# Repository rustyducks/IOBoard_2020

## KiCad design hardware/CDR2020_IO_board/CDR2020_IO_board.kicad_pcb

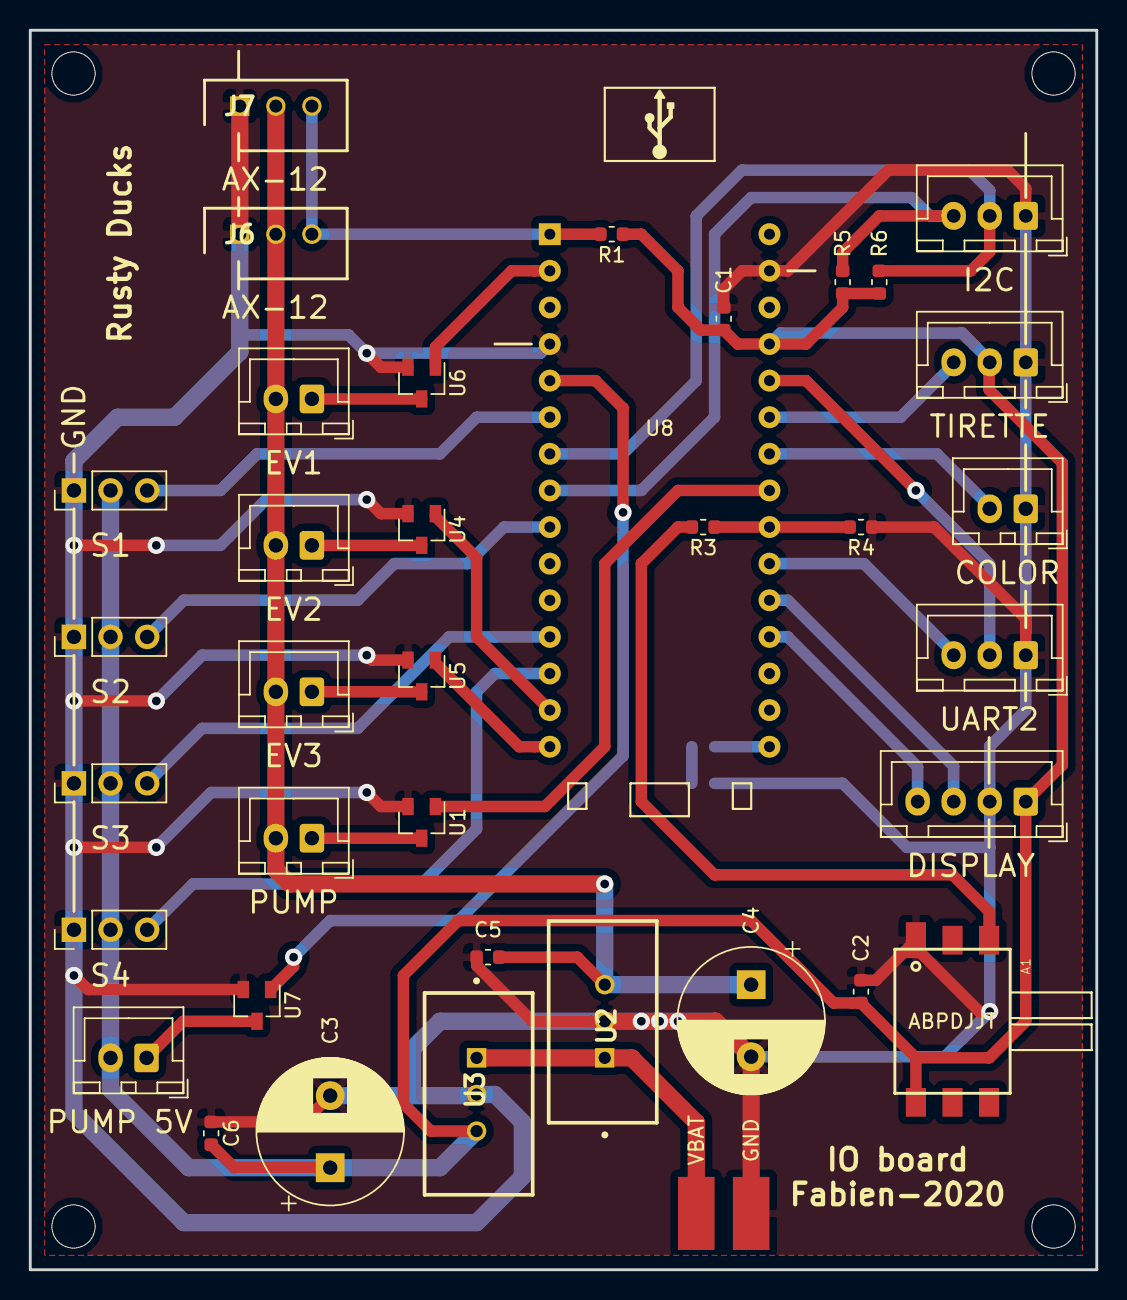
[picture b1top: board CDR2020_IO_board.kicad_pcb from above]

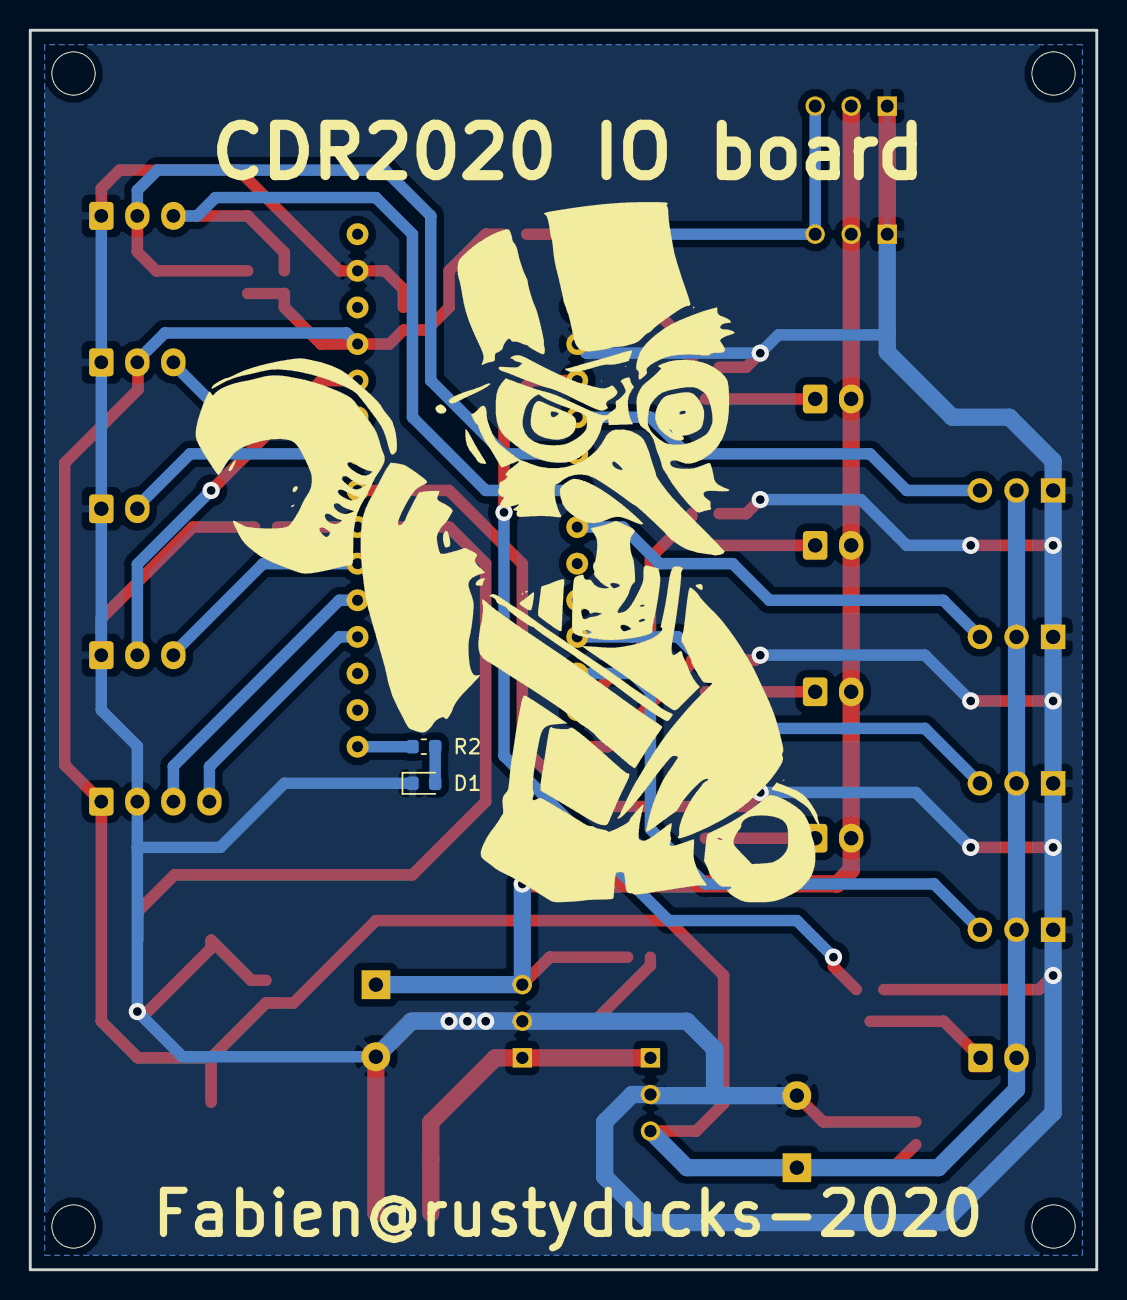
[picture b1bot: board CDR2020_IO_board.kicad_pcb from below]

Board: 2 copper layers, 74.0 x 86.0 mm, 39 parts (2 on the bottom side), 31 nets.

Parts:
A1: ABPDJJT; DIP762W50P254L730H410Q6
C1, C2, C5, C6: 100n; C_0603_1608Metric
C3, C4: C; CP_Radial_D10.0mm_P5.00mm
COLOR: COL; JST_XH_B02B-XH-A_1x02_P2.50mm_Vertical
D1: LED; LED_0603_1608Metric
DISPLAY: DISPLAY; JST_XH_B04B-XH-A_1x04_P2.50mm_Vertical
EV1, EV2, EV3: EV; JST_XH_B02B-XH-A_1x02_P2.50mm_Vertical
I2C: I2C; JST_XH_B03B-XH-A_1x03_P2.50mm_Vertical
J6, J7: 22-03-5035; SHDR3W70P0X250_1X3_990X490X590P
P1: Power_pads
PUMP: EV; JST_XH_B02B-XH-A_1x02_P2.50mm_Vertical
PUMP 5V: EV; JST_XH_B02B-XH-A_1x02_P2.50mm_Vertical
R1: 1k; R_0603_1608Metric
R2: 390; R_0603_1608Metric
R3: 3.3k; R_0603_1608Metric
R4: 6.8k; R_0603_1608Metric
R5, R6: 2.2k; R_0603_1608Metric
S1, S2, S3, S4: SERVO; PinHeader_1x03_P2.54mm_Vertical
TIRETTE: TIR; JST_XH_B03B-XH-A_1x03_P2.50mm_Vertical
U1, U4, U5, U6, U7: IRLML6344; SOT-23
U2: TSR_2-24120; TSR-2
U3: TSR_2-2450; TSR-2
U8: NUCLEO32-L432KC; NUCLEO32
UART2: U2; JST_XH_B03B-XH-A_1x03_P2.50mm_Vertical

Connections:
+5V: A1.6, C1.2, C2.2, C3.1, C6.1, DISPLAY.1, PUMP 5V.2, R1.1, R5.2, R6.2, S1.2, S2.2, S3.2, S4.2, TIRETTE.2, U3.3, U8.27
+12V: C4.1, C5.1, EV1.2, EV2.2, EV3.2, J6.2, J7.2, PUMP.2, U2.3
/ADC: R3.1, R4.2, U8.22
/AN1: DISPLAY.3, U8.20
/AN2: DISPLAY.4, U8.19
/DYN_TX: J6.3, J7.3, R1.2, U8.1
/EV1: U4.1, U8.14
/EV2: U5.1, U8.15
/EV_SENSOR: U1.1, U8.23
/I2C_SCL: I2C.3, R5.1, U8.8
/I2C_SDA: I2C.2, R6.1, U8.7
/PUMP1: U6.1, U8.2
/PUMP2: U7.1, U8.5
/SRV1: S1.3, U8.6
/SRV2: S2.3, U8.9
/SRV3: S3.3, U8.12
/SRV4: S4.3, U8.13
/U2_RX: U8.21, UART2.3
/U2_TX: U8.26, UART2.2
/color: COLOR.2, U8.24
/tirette: TIRETTE.3, U8.25
GND: A1.1, C1.1, C2.1, C3.2, C4.2, C5.2, C6.2, COLOR.1, D1.1, DISPLAY.2, I2C.1, J6.1, J7.1, P1.1, R4.1, S1.1, S2.1, S3.1, S4.1, TIRETTE.1, U1.2, U2.2, U3.2, U4.2, U5.2, U6.2, U7.2, U8.4, U8.29, UART2.1
unnamed: A1.3, R3.2
unnamed: D1.2, R2.2
unnamed: PUMP.1, U1.3
unnamed: EV2.1, U4.3
unnamed: EV3.1, U5.3
unnamed: EV1.1, U6.3
unnamed: PUMP 5V.1, U7.3
unnamed: P1.2, U2.1, U3.1
unnamed: R2.1, U8.16

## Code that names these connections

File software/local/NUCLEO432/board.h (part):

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#define	PA03                           3U
#define	PRESSURE_MEAS                  4U
#define	EV_S                           5U
#define	COLOR                          6U
#define	TIRETTE                        7U
#define	SERVO3                         8U
#define	TERMINAL_TX                    9U
#define	PUMP1                          10U
#define	SERVO4                         11U
#define	PUMP2                          12U
#define	SWDIO                          13U
#define	SWCLK                          14U
#define	VCP_RX                         15U
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					 PIN_MODE_ANALOG(PA03) | \
					 PIN_MODE_ANALOG(PRESSURE_MEAS) | \
					 PIN_MODE_OUTPUT(EV_S) | \
					 PIN_MODE_INPUT(COLOR) | \
					 PIN_MODE_INPUT(TIRETTE) | \
					 PIN_MODE_ALTERNATE(SERVO3) | \
					 PIN_MODE_ALTERNATE(TERMINAL_TX) | \
					 PIN_MODE_OUTPUT(PUMP1) | \
					 PIN_MODE_ALTERNATE(SERVO4) | \
					 PIN_MODE_OUTPUT(PUMP2) | \
					 PIN_MODE_ALTERNATE(SWDIO) | \
					 PIN_MODE_ALTERNATE(SWCLK) | \
					 PIN_MODE_ALTERNATE(VCP_RX))
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					 PIN_OTYPE_PUSHPULL(PA03) | \
					 PIN_OTYPE_PUSHPULL(PRESSURE_MEAS) | \
					 PIN_OTYPE_PUSHPULL(EV_S) | \
					 PIN_OTYPE_OPENDRAIN(COLOR) | \
					 PIN_OTYPE_OPENDRAIN(TIRETTE) | \
					 PIN_OTYPE_PUSHPULL(SERVO3) | \
					 PIN_OTYPE_OPENDRAIN(TERMINAL_TX) | \
					 PIN_OTYPE_PUSHPULL(PUMP1) | \
					 PIN_OTYPE_PUSHPULL(SERVO4) | \
					 PIN_OTYPE_PUSHPULL(PUMP2) | \
					 PIN_OTYPE_PUSHPULL(SWDIO) | \
					 PIN_OTYPE_PUSHPULL(SWCLK) | \
					 PIN_OTYPE_PUSHPULL(VCP_RX))
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					 PIN_OSPEED_SPEED_VERYLOW(PA03) | \
					 PIN_OSPEED_SPEED_VERYLOW(PRESSURE_MEAS) | \
					 PIN_OSPEED_SPEED_VERYLOW(EV_S) | \
					 PIN_OSPEED_SPEED_VERYLOW(COLOR) | \
					 PIN_OSPEED_SPEED_VERYLOW(TIRETTE) | \
					 PIN_OSPEED_SPEED_HIGH(SERVO3) | \
					 PIN_OSPEED_SPEED_HIGH(TERMINAL_TX) | \
					 PIN_OSPEED_SPEED_VERYLOW(PUMP1) | \
					 PIN_OSPEED_SPEED_HIGH(SERVO4) | \
					 PIN_OSPEED_SPEED_VERYLOW(PUMP2) | \
					 PIN_OSPEED_SPEED_HIGH(SWDIO) | \
					 PIN_OSPEED_SPEED_HIGH(SWCLK) | \
					 PIN_OSPEED_SPEED_HIGH(VCP_RX))
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					 PIN_PUPDR_FLOATING(PA03) | \
					 PIN_PUPDR_FLOATING(PRESSURE_MEAS) | \
					 PIN_PUPDR_FLOATING(EV_S) | \
					 PIN_PUPDR_PULLUP(COLOR) | \
					 PIN_PUPDR_PULLUP(TIRETTE) | \
					 PIN_PUPDR_FLOATING(SERVO3) | \
					 PIN_PUPDR_PULLUP(TERMINAL_TX) | \
					 PIN_PUPDR_FLOATING(PUMP1) | \
					 PIN_PUPDR_FLOATING(SERVO4) | \
					 PIN_PUPDR_FLOATING(PUMP2) | \
					 PIN_PUPDR_PULLUP(SWDIO) | \
					 PIN_PUPDR_PULLUP(SWCLK) | \
					 PIN_PUPDR_FLOATING(VCP_RX))
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					 PIN_ODR_LEVEL_HIGH(PA03) | \
					 PIN_ODR_LEVEL_LOW(PRESSURE_MEAS) | \
					 PIN_ODR_LEVEL_LOW(EV_S) | \
					 PIN_ODR_LEVEL_LOW(COLOR) | \
					 PIN_ODR_LEVEL_LOW(TIRETTE) | \
					 PIN_ODR_LEVEL_LOW(SERVO3) | \
					 PIN_ODR_LEVEL_HIGH(TERMINAL_TX) | \
					 PIN_ODR_LEVEL_LOW(PUMP1) | \
					 PIN_ODR_LEVEL_LOW(SERVO4) | \
					 PIN_ODR_LEVEL_LOW(PUMP2) | \
					 PIN_ODR_LEVEL_HIGH(SWDIO) | \
					 PIN_ODR_LEVEL_HIGH(SWCLK) | \
					 PIN_ODR_LEVEL_HIGH(VCP_RX))
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					 PIN_AFIO_AF(PA03, 0) | \
					 PIN_AFIO_AF(PRESSURE_MEAS, 0) | \
					 PIN_AFIO_AF(EV_S, 0) | \
					 PIN_AFIO_AF(COLOR, 0) | \
					 PIN_AFIO_AF(TIRETTE, 0))

#define VAL_GPIOA_AFRH			(PIN_AFIO_AF(SERVO3, 1) | \
					 PIN_AFIO_AF(TERMINAL_TX, 7) | \
					 PIN_AFIO_AF(PUMP1, 0) | \
					 PIN_AFIO_AF(SERVO4, 1) | \
					 PIN_AFIO_AF(PUMP2, 0) | \
					 PIN_AFIO_AF(SWDIO, 0) | \
					 PIN_AFIO_AF(SWCLK, 0) | \
					 PIN_AFIO_AF(VCP_RX, 3))
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					 PIN_ASCR_DISABLED(PA03) | \
					 PIN_ASCR_ENABLED(PRESSURE_MEAS) | \
					 PIN_ASCR_DISABLED(EV_S) | \
					 PIN_ASCR_DISABLED(COLOR) | \
					 PIN_ASCR_DISABLED(TIRETTE) | \
					 PIN_ASCR_DISABLED(SERVO3) | \
					 PIN_ASCR_DISABLED(TERMINAL_TX) | \
					 PIN_ASCR_DISABLED(PUMP1) | \
					 PIN_ASCR_DISABLED(SERVO4) | \
					 PIN_ASCR_DISABLED(PUMP2) | \
					 PIN_ASCR_DISABLED(SWDIO) | \
					 PIN_ASCR_DISABLED(SWCLK) | \
					 PIN_ASCR_DISABLED(VCP_RX))
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					 PIN_LOCKR_DISABLED(PA03) | \
					 PIN_LOCKR_DISABLED(PRESSURE_MEAS) | \
					 PIN_LOCKR_DISABLED(EV_S) | \
					 PIN_LOCKR_DISABLED(COLOR) | \
					 PIN_LOCKR_DISABLED(TIRETTE) | \
					 PIN_LOCKR_DISABLED(SERVO3) | \
					 PIN_LOCKR_DISABLED(TERMINAL_TX) | \
					 PIN_LOCKR_DISABLED(PUMP1) | \
					 PIN_LOCKR_DISABLED(SERVO4) | \
					 PIN_LOCKR_DISABLED(PUMP2) | \
					 PIN_LOCKR_DISABLED(SWDIO) | \
					 PIN_LOCKR_DISABLED(SWCLK) | \
					 PIN_LOCKR_DISABLED(VCP_RX))
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
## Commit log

2020-03-06 IO board 2020
2020-03-10 Begin software. Add TM1637 driver.
2020-03-11 Add crane and actuators command.
2022-02-04 latest changes
2022-05-07 Start software for 2022 Crolonome.
2022-05-10 Crolonome pin layout
2022-05-11 Crolonome init.
2022-05-11 Comm : better parsing.
2022-05-11 Send resistance value and commands electromagnet.
2022-05-11 Fix switch issue.
2022-05-12 config

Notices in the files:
software/local/NUCLEO432/board.h:
ChibiOS - Copyright (C) 2006..2015 Giovanni Di Sirio
Licensed under the Apache License, Version 2.0 (the "License");
